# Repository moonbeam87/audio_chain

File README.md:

# Audio Chain

KiCad designed Audio Chain. Dual channel, switching input, Quad amp IC with possible bluetooth support and LED integration being added

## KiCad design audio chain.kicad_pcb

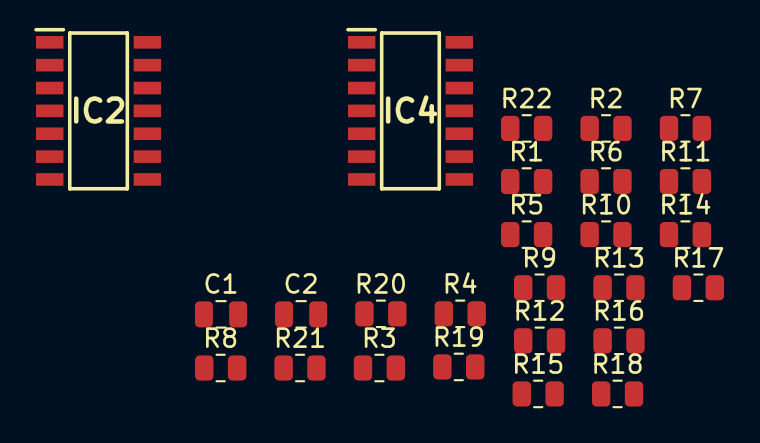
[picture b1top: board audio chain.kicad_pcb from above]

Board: 2 copper layers, 26 parts (0 on the bottom side), 21 nets, no tracks yet.

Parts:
C1, C2: C; C_0805_2012Metric
IC2, IC4: LM2902AWYDT; SOIC127P600X175-14N
R1, R3, R5, R8, R12, R16: 9K; R_0805_2012Metric
R2, R4, R6, R9, R10, R11, R13, R14, R15, R17, R18, R19, R20, R21: 1K; R_0805_2012Metric
R7, R22: 10K; R_0805_2012Metric

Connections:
+12V: IC2.4 (VCC+), IC2.11 (VCC-), IC2.12 (NON-INVERTING_INPUT4), IC4.4, IC4.11, IC4.12, R2.2, R4.2, R6.2, R7.2, R10.2, R13.2, R17.2, R22.2
unnamed: C1.1, R12.2
unnamed: C1.2, R7.1
unnamed: C2.1, IC2.8 (OUTPUT_3), IC4.8, R16.2
unnamed: C2.2, R22.1
unnamed: R1.1, R2.1
unnamed: R5.1, R6.1
unnamed: R12.1, R13.1
unnamed: R9.2, R11.2, R18.1, R19.1
unnamed: R18.2, R19.2
unnamed: IC2.1 (OUTPUT_1), IC2.5 (NON-INVERTING_INPUT2), R3.2
unnamed: IC2.2 (INVERTING_INPUT1), R3.1, R4.1
unnamed: IC2.6 (INVERTING_INPUT_2), R8.1, R10.1
unnamed: IC2.9 (INVERTING_INPUT3), R16.1, R17.1
unnamed: IC2.7 (OUTPUT2), IC2.10 (NON-INVERTING_INPUT3), R8.2
unnamed: IC2.13 (INVERTING_INPUT_4), R14.2, R15.2, R20.1, R21.1
unnamed: IC2.14 (OUTPUT_4), R20.2, R21.2
unnamed: IC4.1, IC4.5
unnamed: IC4.7, IC4.10
unnamed: R9.1, R11.1
unnamed: R14.1, R15.1

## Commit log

2021-12-04 initial
2021-12-05 added transistor footprint
